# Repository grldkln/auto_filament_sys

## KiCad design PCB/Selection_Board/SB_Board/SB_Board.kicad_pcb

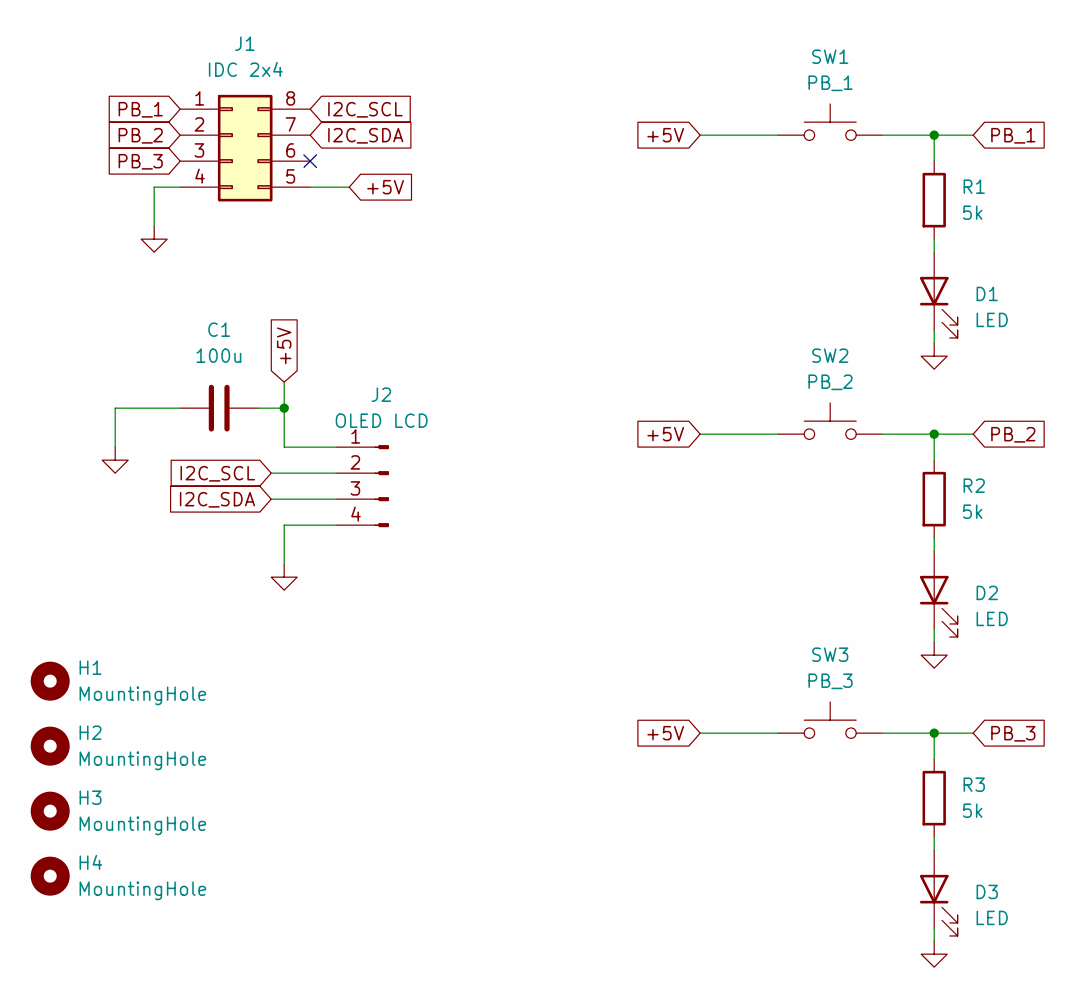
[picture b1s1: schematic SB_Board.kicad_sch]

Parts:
C1: 100u; C_Radial_D6.3mm_H11.0mm_P2.50mm
D1, D2, D3: LED; LED_0603_1608Metric
H1, H2, H3, H4: MountingHole; MountingHole_3.2mm_M3
J1: IDC 2x4; IDC-Header_2x04_P2.54mm_Horizontal
J2: OLED LCD; JST_XH_B4B-XH-AM_1x04_P2.50mm_Vertical
R1, R2, R3: 5k; R_0402_1005Metric
SW1: PB_1; SW_SPST_Omron_B3F-40xx
SW2: PB_2; SW_SPST_Omron_B3F-40xx
SW3: PB_3; SW_SPST_Omron_B3F-40xx

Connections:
+5V: C1.2, J1.5, J2.1, SW1.1, SW2.1, SW3.1
GND: C1.1, D1.1 (K), D2.1 (K), D3.1 (K), J1.4, J2.4
I2C_SCL: J1.8, J2.2
I2C_SDA: J1.7, J2.3
unnamed: D1.2 (A), R1.2
unnamed: D2.2 (A), R2.2
unnamed: D3.2 (A), R3.2
PB_1: J1.1, R1.1, SW1.2
PB_2: J1.2, R2.1, SW2.2
PB_3: J1.3, R3.1, SW3.2

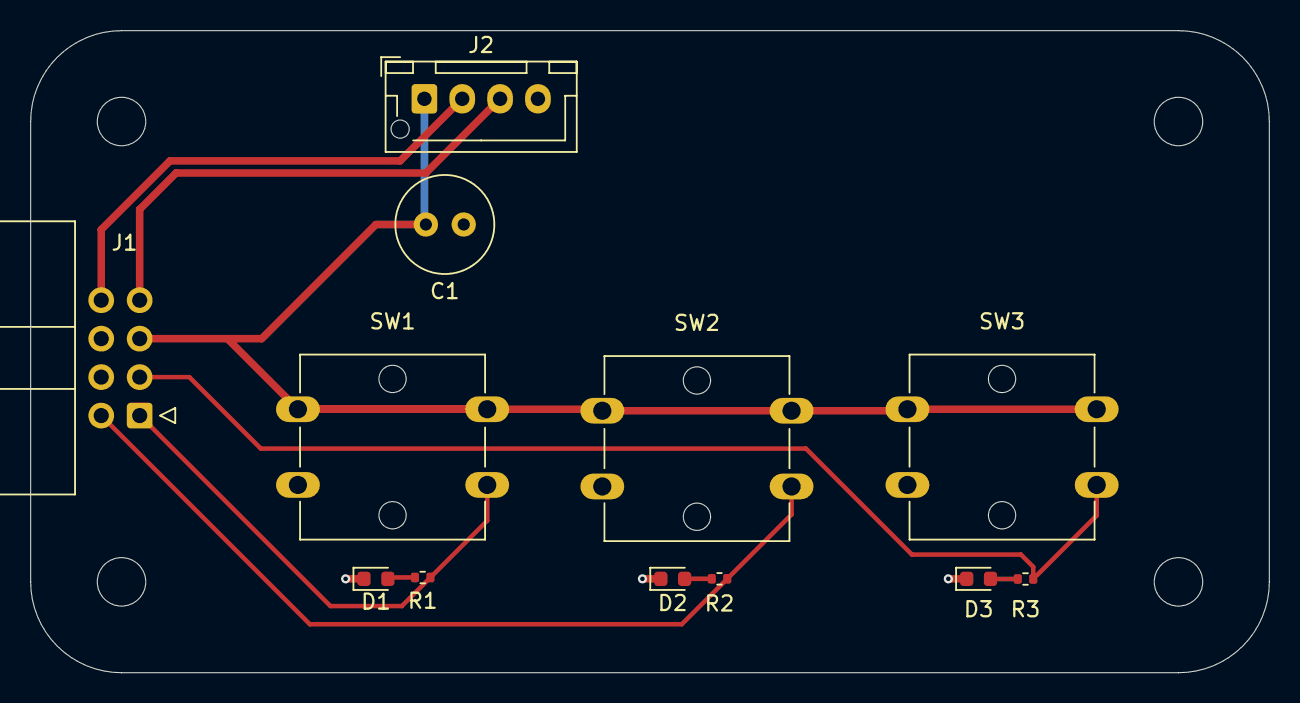
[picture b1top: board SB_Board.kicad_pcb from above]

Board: 2 copper layers, 81.8 x 42.4 mm, 16 parts (0 on the bottom side), 10 nets.

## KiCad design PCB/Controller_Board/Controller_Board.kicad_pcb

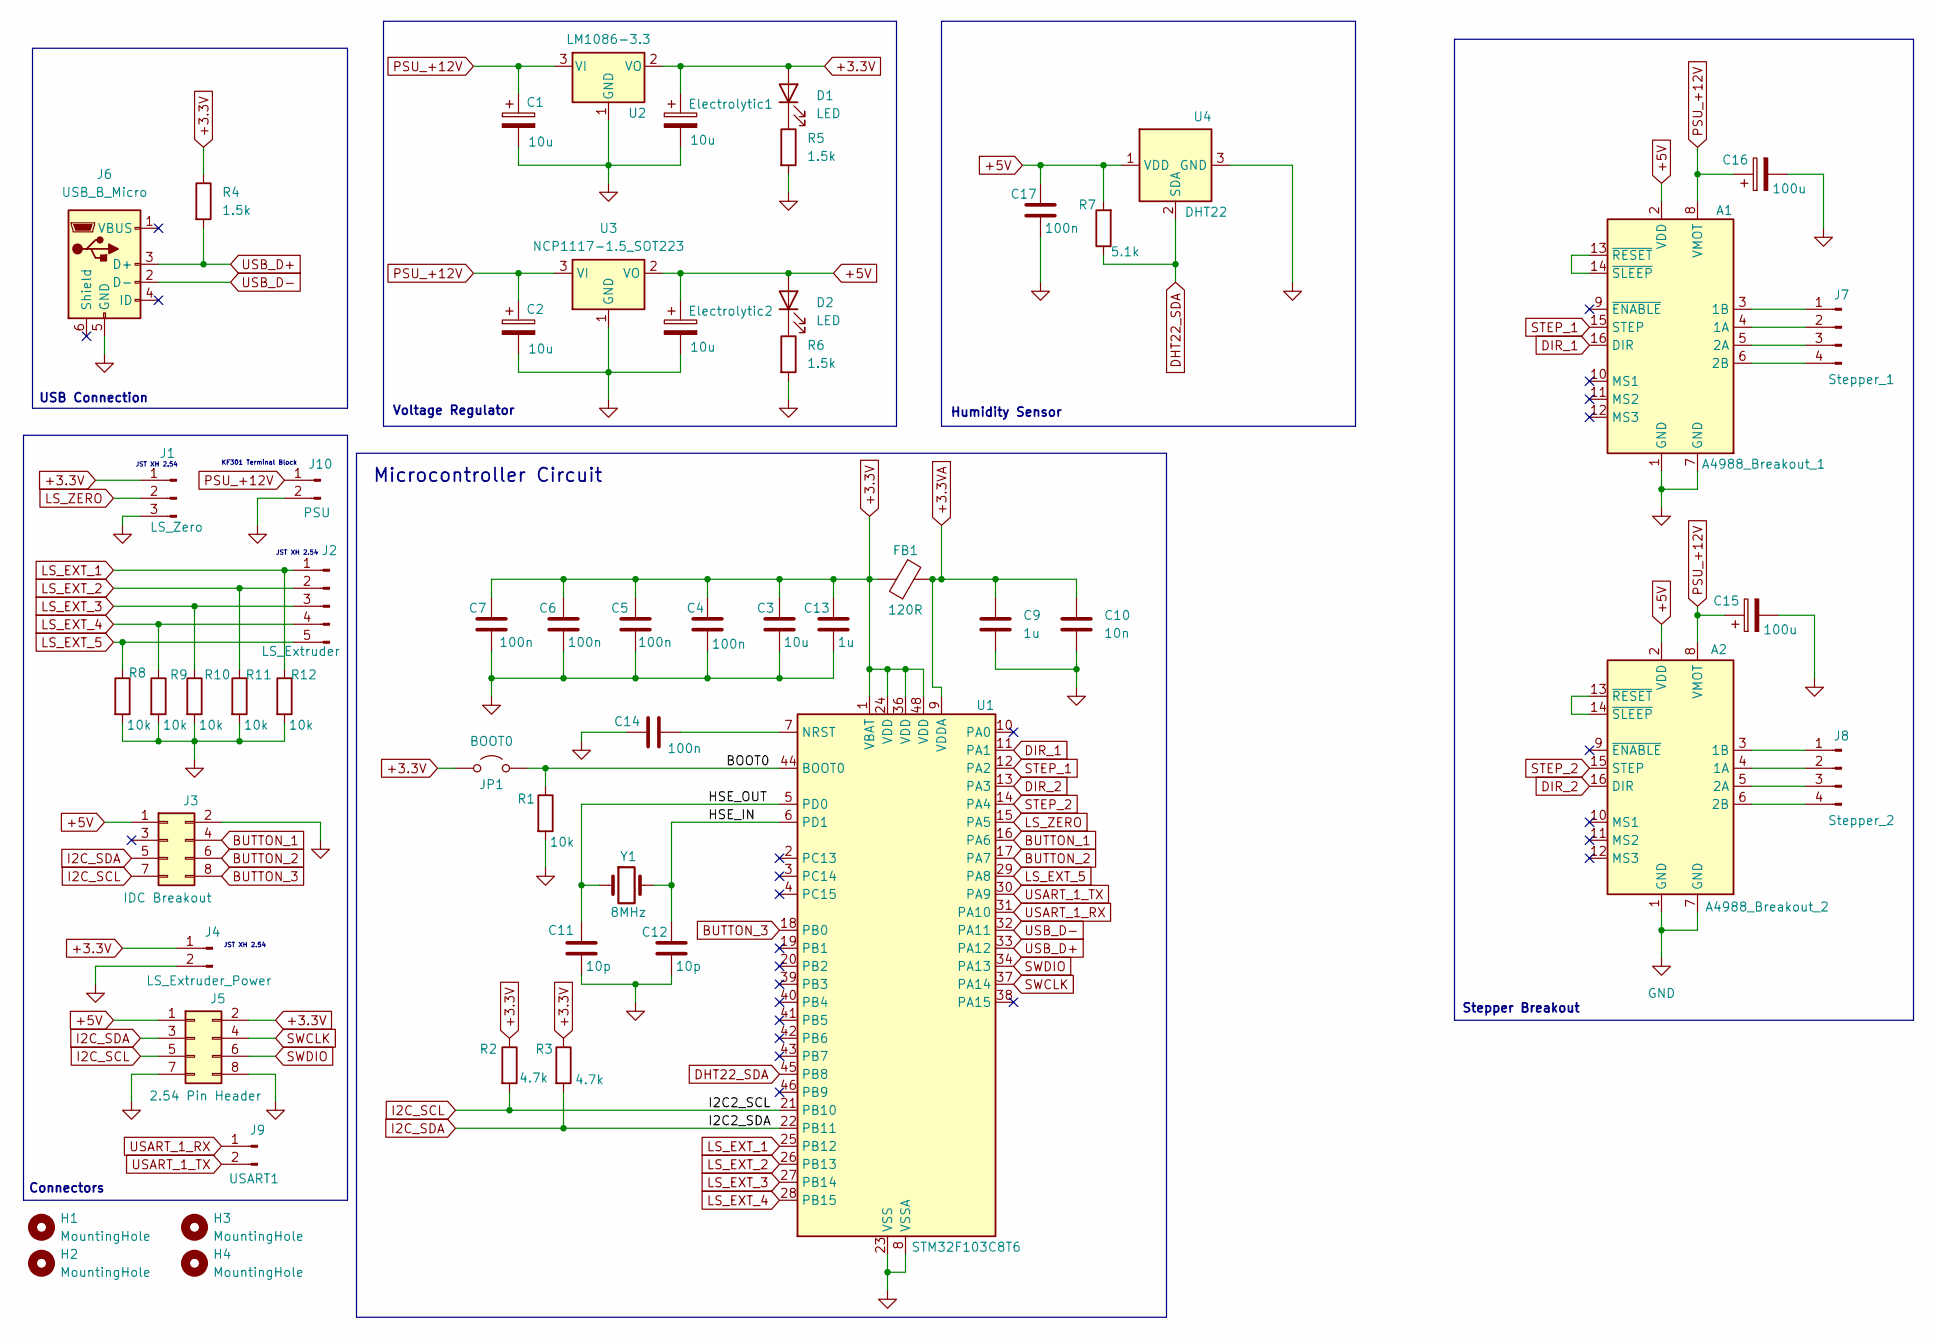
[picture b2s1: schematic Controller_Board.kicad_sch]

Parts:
A1: A4988_Breakout_1; Pololu_Breakout-16_15.2x20.3mm
A2: A4988_Breakout_2; Pololu_Breakout-16_15.2x20.3mm
C1, C2, C3: 10u; C_0805_2012Metric
C4, C5, C6, C7, C14, C17: 100n; C_0402_1005Metric
C9, C13: 1u; C_0402_1005Metric
C10: 10n; C_0402_1005Metric
C11, C12: 10p; C_0402_1005Metric
C15, C16: 100u; C_Radial_D6.3mm_H11.0mm_P2.50mm
D1, D2: LED; LED_0603_1608Metric
Electrolytic1, Electrolytic2: 10u; CP_Elec_5x5.4
FB1: 120R; L_0603_1608Metric
H1, H2, H3, H4: MountingHole; MountingHole_3.2mm_M3
J1: LS_Zero; JST_XH_B3B-XH-A_1x03_P2.50mm_Vertical
J2: LS_Extruder; JST_XH_B5B-XH-A_1x05_P2.50mm_Vertical
J3: IDC Breakout; IDC-Header_2x04_P2.54mm_Vertical
J4: LS_Extruder_Power; JST_XH_B2B-XH-A_1x02_P2.50mm_Vertical
J5: 2.54 Pin Header; PinHeader_2x04_P2.54mm_Vertical
J6: USB_B_Micro; MICRO-USB-SMD_5P-P0.65-H-F_C10418
J7: Stepper_1; JST_XH_B4B-XH-A_1x04_P2.50mm_Vertical
J8: Stepper_2; JST_XH_B4B-XH-A_1x04_P2.50mm_Vertical
J9: USART1; PinHeader_1x02_P2.54mm_Vertical
J10: PSU; TerminalBlock_RND_205-00232_1x02_P5.08mm_Horizontal
JP1: BOOT0; PinHeader_1x02_P2.54mm_Vertical
R1, R8, R9, R10, R11, R12: 10k; R_0402_1005Metric
R2, R3: 4.7k; R_0402_1005Metric
R4, R5, R6: 1.5k; R_0402_1005Metric
R7: 5.1k; R_0402_1005Metric
U1: STM32F103C8T6; LQFP-48_7x7mm_P0.5mm
U2: LM1086-3.3; TO-263-3_TabPin2
U3: NCP1117-1.5_SOT223; SOT-223-3_TabPin2
U4: DHT22; ASAIR_AM2302_P2.54mm_Vertical
Y1: 8MHz; Crystal_HC49-U_Vertical

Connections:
+3.3V: C3.1, C4.1, C5.1, C6.1, C7.1, C13.1, D1.2 (A), Electrolytic1.1, FB1.1, J1.1, J4.1, J5.2, JP1.1 (A), R2.1, R3.1, R4.1, U1.1 (VBAT), U1.24 (VDD), U1.36 (VDD), U1.48 (VDD), U2.2 (VO)
+3.3VA: C9.1, C10.1, FB1.2, U1.9 (VDDA)
+5V: A1.2 (VDD), A2.2 (VDD), C17.1, D2.2 (A), Electrolytic2.1, J3.1, J5.1, R7.2, U3.2 (VO), U4.1 (VDD)
/BOOT0: JP1.2 (B), R1.1, U1.44 (BOOT0)
/HSE_IN: C12.1, U1.6 (PD1), Y1.2
/HSE_OUT: C11.1, U1.5 (PD0), Y1.1
BUTTON_1: J3.4, U1.16 (PA6)
BUTTON_2: J3.6, U1.17 (PA7)
BUTTON_3: J3.8, U1.18 (PB0)
DHT22_SDA: R7.1, U1.45 (PB8), U4.2 (SDA)
DIR_1: A1.16 (DIR), U1.11 (PA1)
DIR_2: A2.16 (DIR), U1.13 (PA3)
GND: A1.1 (GND), A1.7 (GND), A2.1 (GND), A2.7 (GND), C1.2, C2.2, C3.2, C4.2, C5.2, C6.2, C7.2, C9.2, C10.2, C11.2, C12.2, C13.2, C14.1, C15.2, C16.2, C17.2, Electrolytic1.2, Electrolytic2.2, J1.3, J3.2, J4.2, J5.7, J5.8, J6.5 (GND), J10.2, R1.2, R5.2, R6.2, R8.2, R9.2, R10.2, R11.2, R12.2, U1.8 (VSSA), U1.23 (VSS), U1.35 (VSS), U1.47 (VSS), U2.1 (GND), U3.1 (GND), U4.3 (GND), U4.4 (GND)
I2C_SCL: J3.7, J5.5, R2.2, U1.21 (PB10)
I2C_SDA: J3.5, J5.3, R3.2, U1.22 (PB11)
LS_EXT_1: J2.1, R12.1, U1.25 (PB12)
LS_EXT_2: J2.2, R11.1, U1.26 (PB13)
LS_EXT_3: J2.3, R10.1, U1.27 (PB14)
LS_EXT_4: J2.4, R9.1, U1.28 (PB15)
LS_EXT_5: J2.5, R8.1, U1.29 (PA8)
LS_ZERO: J1.2, U1.15 (PA5)
unnamed: A1.4 (1A), J7.2
unnamed: A1.3 (1B), J7.1
unnamed: A1.5 (2A), J7.3
unnamed: A1.6 (2B), J7.4
unnamed: A1.13 (~RESET), A1.14 (~SLEEP)
unnamed: A2.4 (1A), J8.2
unnamed: A2.3 (1B), J8.1
unnamed: A2.5 (2A), J8.3
unnamed: A2.6 (2B), J8.4
unnamed: A2.13 (~RESET), A2.14 (~SLEEP)
unnamed: D1.1 (K), R5.1
unnamed: D2.1 (K), R6.1
unnamed: C14.2, U1.7 (NRST)
PSU_+12V: A1.8 (VMOT), A2.8 (VMOT), C1.1, C2.1, C15.1, C16.1, J10.1, U2.3 (VI), U3.3 (VI)
STEP_1: A1.15 (STEP), U1.12 (PA2)
STEP_2: A2.15 (STEP), U1.14 (PA4)
SWCLK: J5.4, U1.37 (PA14)
SWDIO: J5.6, U1.34 (PA13)
USART_1_RX: J9.1, U1.31 (PA10)
USART_1_TX: J9.2, U1.30 (PA9)
USB_D+: J6.3 (D+), R4.2, U1.33 (PA12)
USB_D-: J6.2 (D-), U1.32 (PA11)

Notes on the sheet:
Connectors
JST XH 2.54
USB Connection
KF301 Terminal Block
Humidity Sensor
Stepper Breakout
Microcontroller Circuit
Voltage Regulator

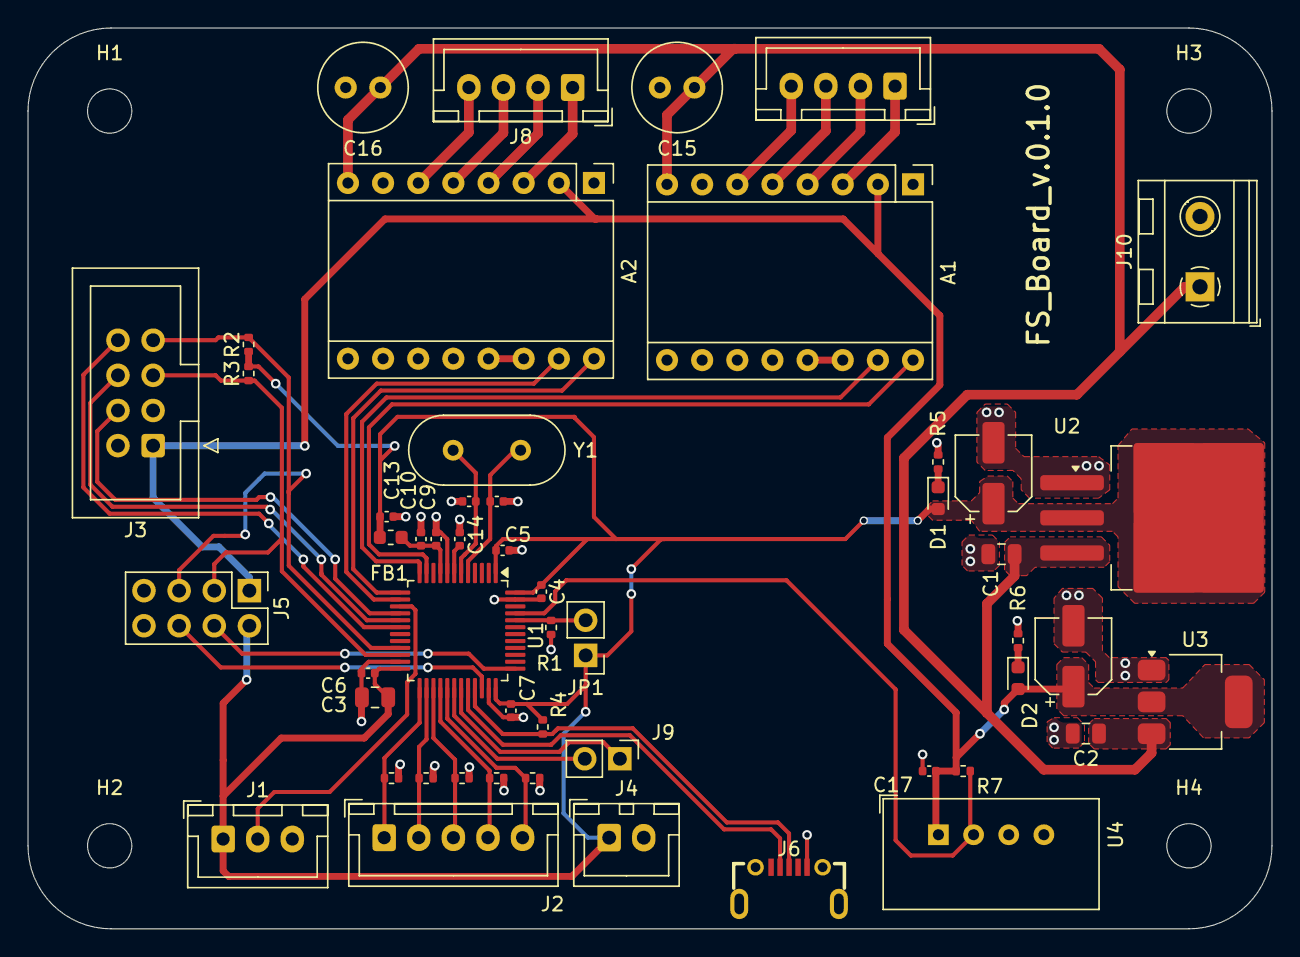
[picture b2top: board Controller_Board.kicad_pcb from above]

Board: 2 copper layers, 89.9 x 65.1 mm, 55 parts (0 on the bottom side), 43 nets.

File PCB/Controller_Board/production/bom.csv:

Designator,Footprint,Quantity,Value,LCSC Part #
A1,Pololu_Breakout-16_15.2x20.3mm,1,A4988_Breakout_1,
A2,Pololu_Breakout-16_15.2x20.3mm,1,A4988_Breakout_2,
"C1, C2, C3",0805,3,10u,
C10,0402,1,10n,
"C11, C12",0402,2,10p,
"C13, C9",0402,2,1u,
"C14, C17, C4, C5, C6, C7",0402,6,100n,
"C15, C16",C_Radial_D6.3mm_H11.0mm_P2.50mm,2,100u,
"D1, D2",0603,2,LED,
"ELECTROLYTIC1, ELECTROLYTIC2",CP_Elec_5x5.4,2,10u,
FB1,0603,1,120R,
J1,JST_XH_B3B-XH-A_1x03_P2.50mm_Vertical,1,LS_Zero,
J10,TerminalBlock_RND_205-00232_1x02_P5.08mm_Horizontal,1,PSU,
J2,JST_XH_B5B-XH-A_1x05_P2.50mm_Vertical,1,LS_Extruder,
J3,IDC-Header_2x04_P2.54mm_Vertical,1,IDC Breakout,
J4,JST_XH_B2B-XH-A_1x02_P2.50mm_Vertical,1,LS_Extruder_Power,
J5,PinHeader_2x04_P2.54mm_Vertical,1,2.54 Pin Header,
J6,MICRO-USB-SMD_5P-P0.65-H-F_C10418,1,USB_B_Micro,
J7,JST_XH_B4B-XH-A_1x04_P2.50mm_Vertical,1,Stepper_1,
J8,JST_XH_B4B-XH-A_1x04_P2.50mm_Vertical,1,Stepper_2,
J9,PinHeader_1x02_P2.54mm_Vertical,1,USART1,
JP1,PinHeader_1x02_P2.54mm_Vertical,1,BOOT0,
"R1, R10, R11, R12, R8, R9",0402,6,10k,
"R2, R3",0402,2,4.7k,
"R4, R5, R6",0402,3,1.5k,
R7,0402,1,5.1k,
U1,LQFP-48_7x7mm_P0.5mm,1,STM32F103C8T6,
U2,TO-263-3_TabPin2,1,LM1086-3.3,
U3,SOT-223-3_TabPin2,1,NCP1117-1.5_SOT223,
U4,ASAIR_AM2302_P2.54mm_Vertical,1,DHT22,
Y1,Crystal_HC49-U_Vertical,1,8MHz,

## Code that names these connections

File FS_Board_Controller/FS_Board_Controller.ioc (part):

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Mcu.Name=STM32F103C(8-B)Tx
Mcu.Package=LQFP48
Mcu.UserName=STM32F103C8Tx
PA1.Signal=GPIO_Output
PA10.Mode=Asynchronous
PA10.Signal=USART1_RX
PA11.Mode=Device
PA11.Signal=USB_DM
PA12.Mode=Device
PA12.Signal=USB_DP
PA13.Mode=Serial_Wire
PA13.Signal=SYS_JTMS-SWDIO
PA14.Mode=Serial_Wire
PA14.Signal=SYS_JTCK-SWCLK
PA2.Signal=GPIO_Output
PA3.Signal=GPIO_Output
PA4.Signal=GPIO_Output
PA5.Signal=GPIO_Input
PA6.Signal=GPIO_Input
PA7.Signal=GPIO_Input
PA8.Signal=GPIO_Input
PA9.Mode=Asynchronous
PA9.Signal=USART1_TX
PB0.Signal=GPIO_Input
PB10.Mode=I2C
PB10.Signal=I2C2_SCL
PB11.Mode=I2C
PB11.Signal=I2C2_SDA
PB12.Signal=GPIO_Input
PB13.Signal=GPIO_Input
PB14.Signal=GPIO_Input
PB15.Signal=GPIO_Input
PB8.Signal=GPIO_Input
PD0-OSC_IN.Mode=HSE-External-Oscillator
PD0-OSC_IN.Signal=RCC_OSC_IN
PD1-OSC_OUT.Mode=HSE-External-Oscillator
PD1-OSC_OUT.Signal=RCC_OSC_OUT
RCC.SYSCLKFreq_VALUE=72000000
RCC.SYSCLKSource=RCC_SYSCLKSOURCE_PLLCLK
board=custom
